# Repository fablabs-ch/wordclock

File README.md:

# WordClock

This is our adaptation of the [Javelin's Word Clock][javelin-word-clock].

## Documentation

You can find all the documentation in the [Wiki][wiki]

* [User manual][user-manual]

## Initial development

The initial development take place on different platforms:

- [Trello][trello-fablabs-ch] for the tasks and progression management.
- [Slack's `#fab-jam_make-athon` channel][slack-fab-jam] for discussions.

## License

This work is licensed under a
[Creative Commons Attribution-NonCommercial-ShareAlike 4.0 International License][by-nc-sa].
Some files may be released under a different license. When this is the case the
license is specified in the file header. This is mainly used for software codes
for which Creative Commons licenses are not well suited.

[][by-nc-sa]

[javelin-word-clock]: http://www.instructables.com/id/Javelins-Word-Clock/
[wiki]: https://github.com/fablabs-ch/wordclock/wiki
[user-manual]: https://github.com/fablabs-ch/wordclock/wiki/User-manual
[trello-fablabs-ch]: https://trello.com/fablabsuisses
[slack-fab-jam]: https://fablabs-ch.slack.com/messages/fab-jam_make-athon/details/
[by-nc-sa]: http://creativecommons.org/licenses/by-nc-sa/4.0/

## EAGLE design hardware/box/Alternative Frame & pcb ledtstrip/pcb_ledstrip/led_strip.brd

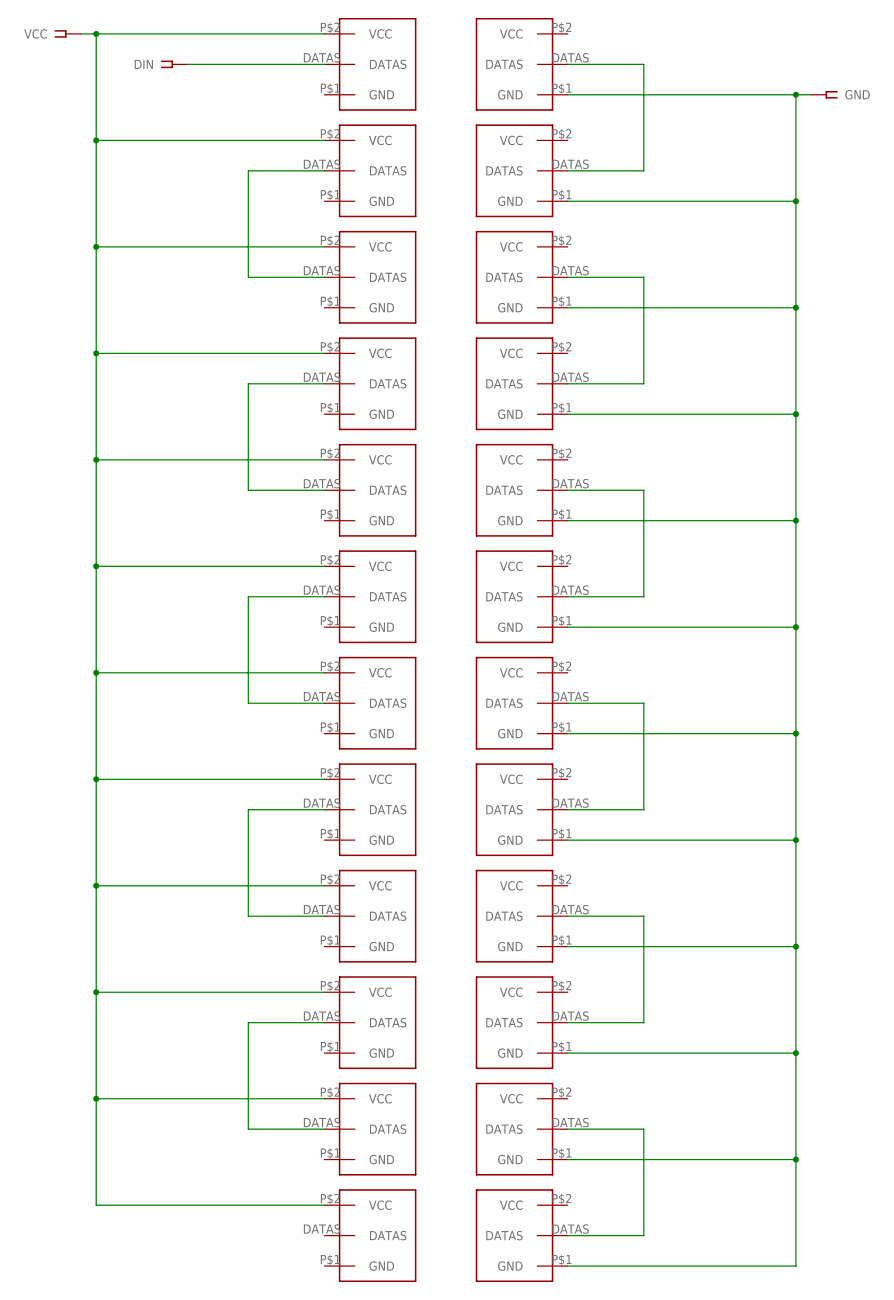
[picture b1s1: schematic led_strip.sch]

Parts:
1: 1; LED_STRIP
2, 3, 4, 5, 6, 7, 8, 9, 10, 11, 12, 13, 14, 15, 16, 17, 18, 19, 20, 21, 22, 23, 24: LED_STRIP
DIN: DATA; SSW-101-02-S-S
GND: GND; SSW-101-02-S-S
VCC: VCC; SSW-101-02-S-S

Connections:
GND: 1.P$1 (GND), 2.P$1 (GND), 3.P$1 (GND), 4.P$1 (GND), 5.P$1 (GND), 6.P$1 (GND), 7.P$1 (GND), 8.P$1 (GND), 9.P$1 (GND), 10.P$1 (GND), 11.P$1 (GND), 12.P$1 (GND), GND.1
unnamed: 13.DATAS, DIN.1
unnamed: 1.DATAS, 2.DATAS
unnamed: 14.DATAS, 15.DATAS
unnamed: 3.DATAS, 4.DATAS
unnamed: 16.DATAS, 17.DATAS
unnamed: 5.DATAS, 6.DATAS
unnamed: 18.DATAS, 19.DATAS
unnamed: 7.DATAS, 8.DATAS
unnamed: 20.DATAS, 21.DATAS
unnamed: 22.DATAS, 23.DATAS
unnamed: 9.DATAS, 10.DATAS
unnamed: 11.DATAS, 12.DATAS
VCC: 13.P$2 (VCC), 14.P$2 (VCC), 15.P$2 (VCC), 16.P$2 (VCC), 17.P$2 (VCC), 18.P$2 (VCC), 19.P$2 (VCC), 20.P$2 (VCC), 21.P$2 (VCC), 22.P$2 (VCC), 23.P$2 (VCC), 24.P$2 (VCC), VCC.1

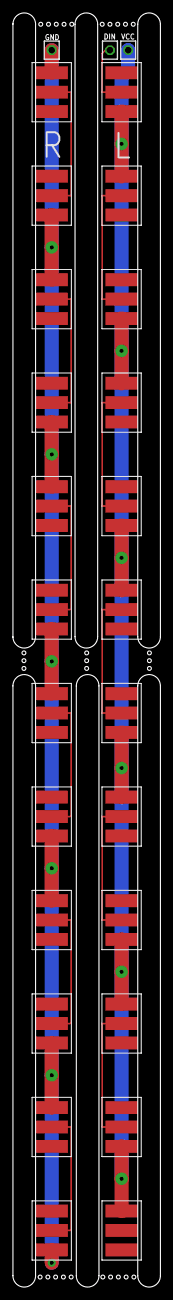
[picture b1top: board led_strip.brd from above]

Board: 2 copper layers, 22.8 x 197.0 mm, 27 parts (0 on the bottom side), 14 nets.

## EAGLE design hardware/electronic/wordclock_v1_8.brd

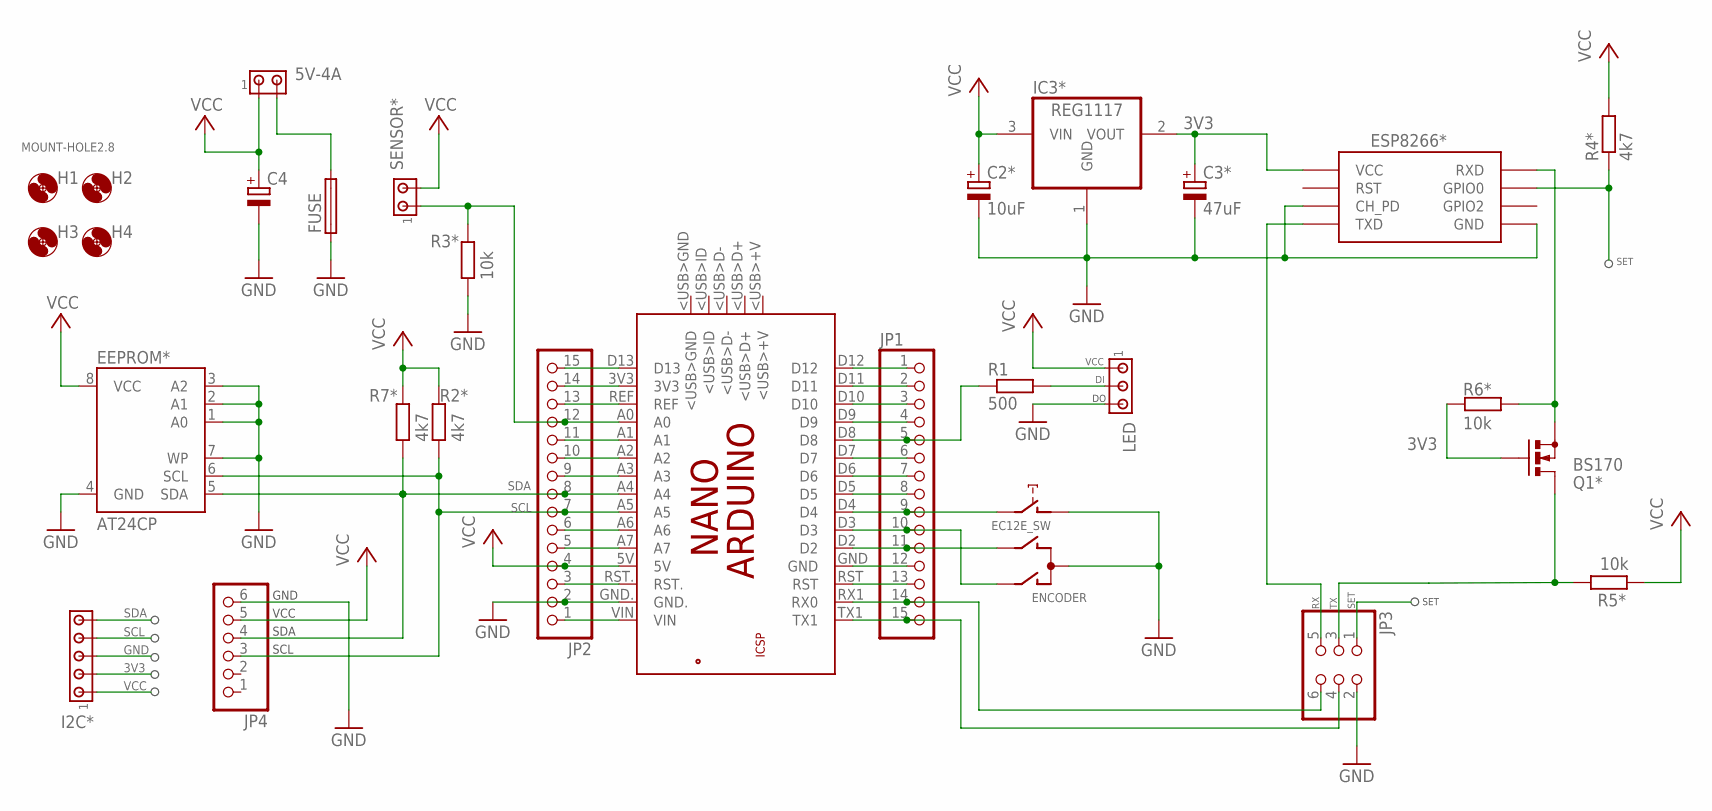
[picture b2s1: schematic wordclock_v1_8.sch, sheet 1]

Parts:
5V-4A: 5V-4A; 1X2MTA
C2*: 10uF; B45181A
C3*: 47uF; B45181A
C4: CPOL-EUE5-10.5; E5-10,5
EEPROM*: AT24CP; DIL08
ENCODER: EC12E_SW; ALPS_EC12E_SW
ESP8266*: ESP01
FUSE: FUSELITTLEFUSE; LITTLEFUSE
H1, H2, H3, H4: MOUNT-HOLE2.8; 2,8
I2C*: MTA05-100; 10X05MTA
IC3*: REG1117; SOT223
JP1, JP2: PINHD-1X15; 1X15
JP3: PINHD-2X3; 2X03
JP4: PINHD-1X6; 1X06
LED: MTA03-156; 1X3MTA
PCB2: ARDUINO_NANO
Q1*: BS170; SOT54E
R1: 500; 0207/7
R2*, R4*, R7*: 4k7; 0207/10
R3*, R5*, R6*: 10k; 0207/10
SENSOR*: MTA02-156; 1X2MTA

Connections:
3V3: C3*.+, ESP8266*.VCC, I2C*.2, IC3*.2 (VOUT), Q1*.G, R6*.1
DI: LED.2, R1.2
GND: C2*.-, C3*.-, C4.-, EEPROM*.1 (A0), EEPROM*.2 (A1), EEPROM*.3 (A2), EEPROM*.4 (GND), EEPROM*.7 (WP), ENCODER.C, ENCODER.D (1), ESP8266*.CH_PD, ESP8266*.GND, FUSE.1, I2C*.3, IC3*.1 (GND), JP2.2, JP3.2, JP4.6, LED.3, PCB2.GND., R3*.1
unnamed: JP1.1, PCB2.D12
unnamed: JP1.2, PCB2.D11
unnamed: JP1.5, PCB2.D8, R1.1
unnamed: 5V-4A.2, FUSE.2
unnamed: ENCODER.B, JP1.11, PCB2.D2
unnamed: ENCODER.A, JP1.10, PCB2.D3
unnamed: ENCODER.E (2), JP1.9, PCB2.D4
unnamed: JP1.3, PCB2.D10
unnamed: JP1.14, JP3.6, PCB2.RX1 (RX0)
unnamed: JP1.15, JP3.4, PCB2.TX1
unnamed: JP2.12, PCB2.A0, R3*.2, SENSOR*.1
unnamed: JP1.4, PCB2.D9
unnamed: JP1.6, PCB2.D7
unnamed: ESP8266*.RX (RXD), Q1*.S, R6*.2
unnamed: JP1.7, PCB2.D6
unnamed: JP1.8, PCB2.D5
unnamed: JP1.12, PCB2.GND
unnamed: JP1.13, PCB2.RST
unnamed: JP2.15, PCB2.D13
unnamed: JP2.14, PCB2.3V3
unnamed: JP2.13, PCB2.REF
unnamed: JP2.11, PCB2.A1
unnamed: JP2.10, PCB2.A2
unnamed: JP2.9, PCB2.A3
unnamed: JP2.6, PCB2.A6
unnamed: JP2.5, PCB2.A7
unnamed: JP2.3, PCB2.RST.
unnamed: JP2.1, PCB2.VIN
RX: ESP8266*.TX (TXD), JP3.5
SCL: EEPROM*.6 (SCL), I2C*.4, JP2.7, JP4.3, PCB2.A5, R2*.1
SDA: EEPROM*.5 (SDA), I2C*.5, JP2.8, JP4.4, PCB2.A4, R7*.1
SET: ESP8266*.GPIO0, JP3.1, R4*.1
TX: JP3.3, Q1*.D, R5*.2
VCC: 5V-4A.1, C2*.+, C4.+, EEPROM*.8 (VCC), I2C*.1, IC3*.3 (VIN), JP2.4, JP4.5, LED.1, PCB2.5V, R2*.2, R4*.2, R5*.1, R7*.2, SENSOR*.2

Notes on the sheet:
SDA
SCL
GND
VCC
SET

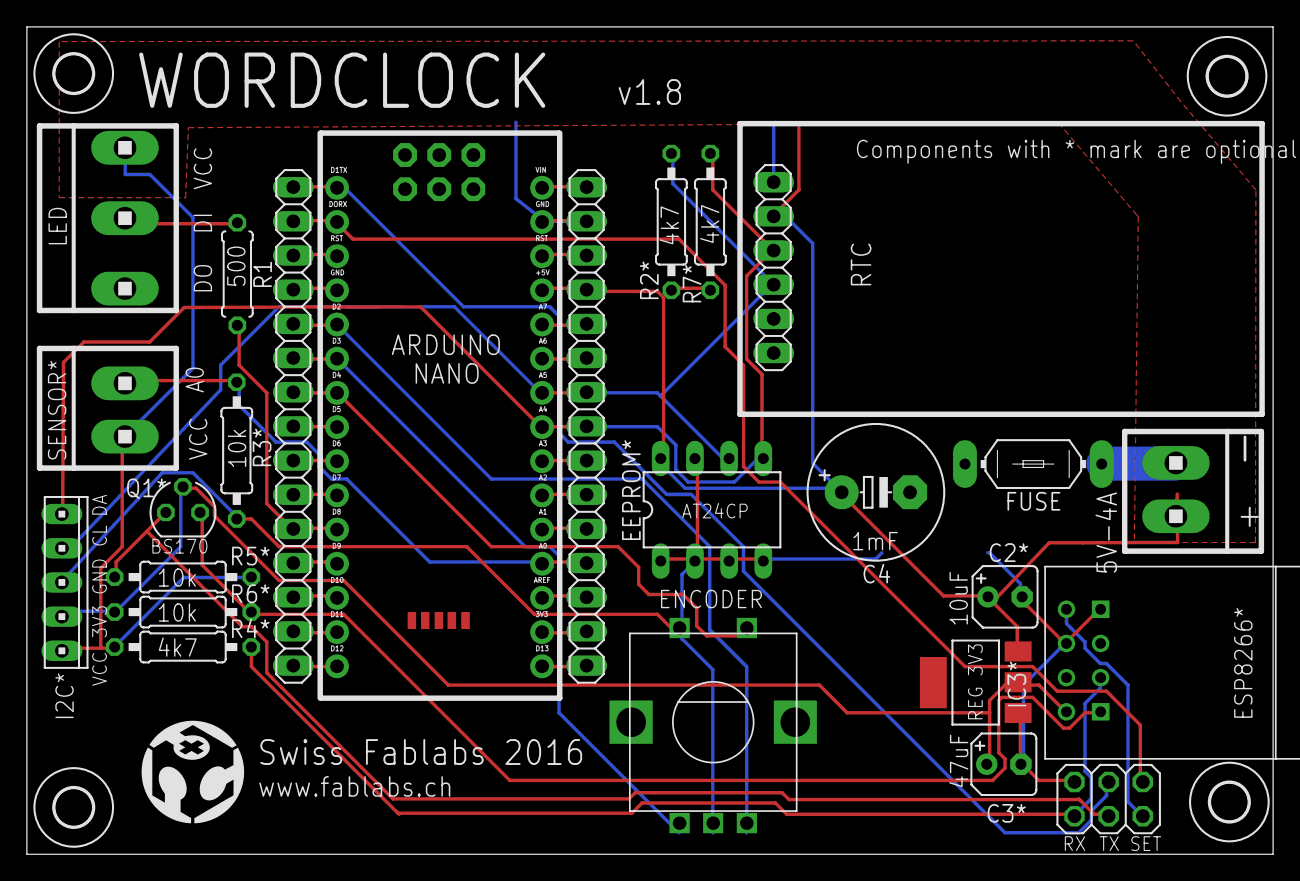
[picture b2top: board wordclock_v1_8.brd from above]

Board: 2 copper layers, 92.6 x 61.5 mm, 29 parts (0 on the bottom side), 37 nets.

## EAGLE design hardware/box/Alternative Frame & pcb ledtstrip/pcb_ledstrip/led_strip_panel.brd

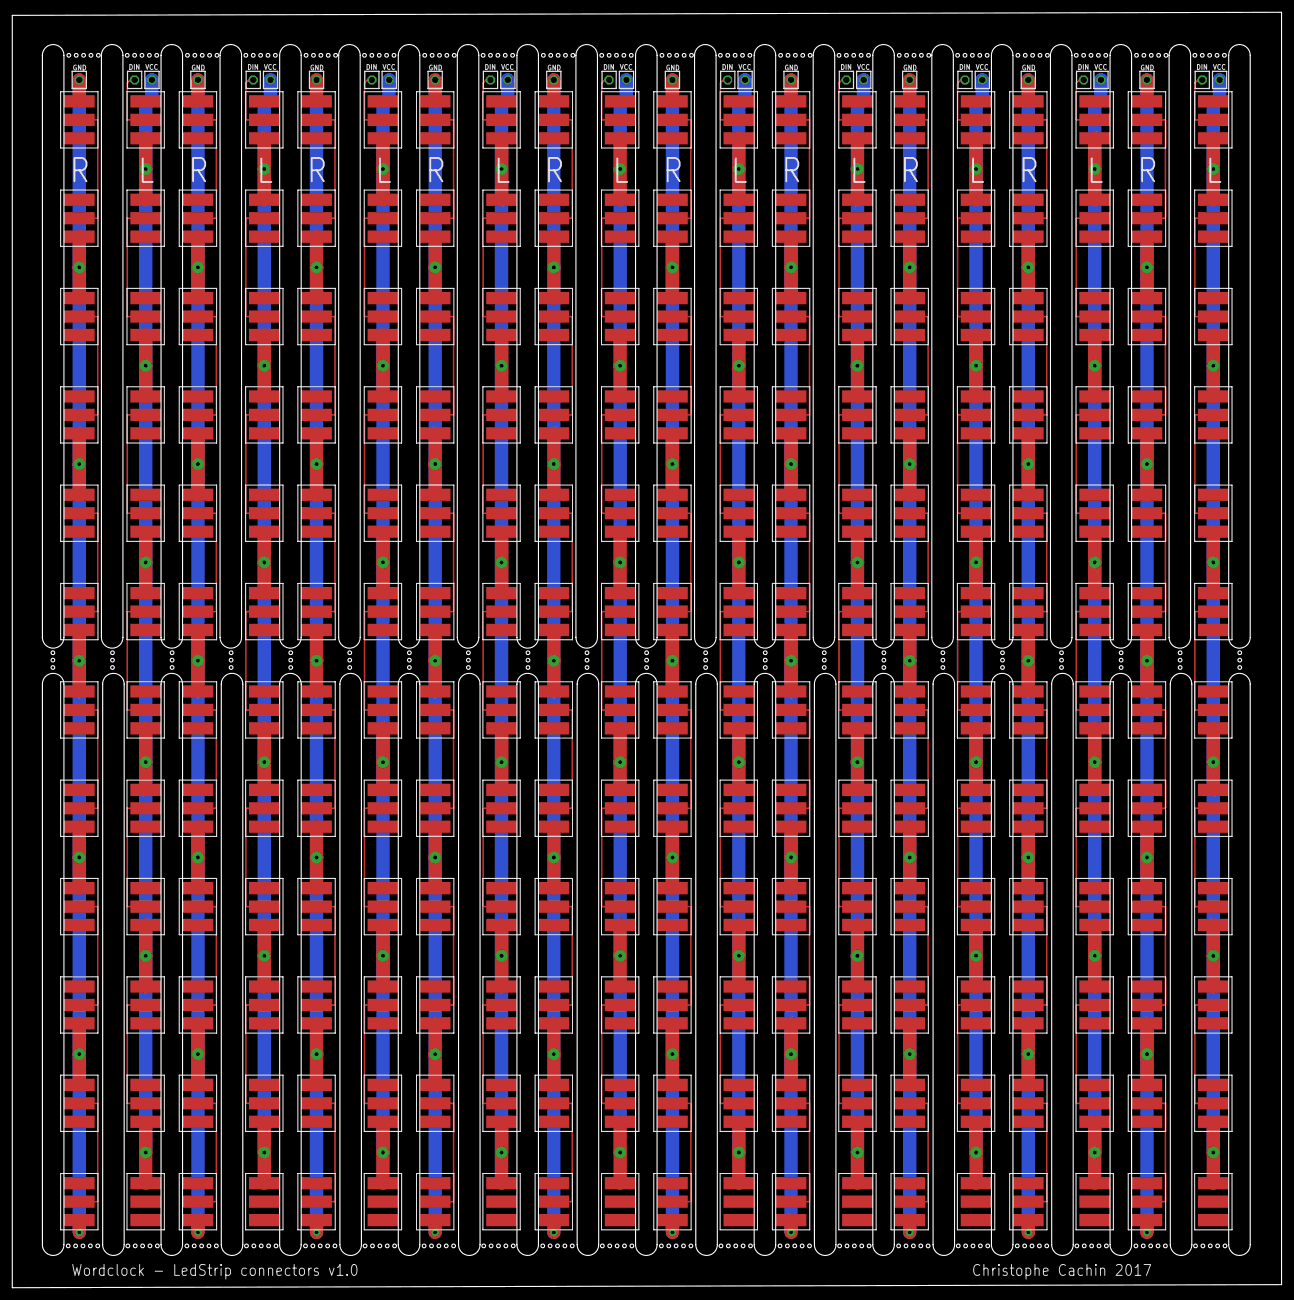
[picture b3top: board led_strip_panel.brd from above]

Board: 2 copper layers, 206.5 x 207.5 mm, 270 parts (0 on the bottom side), 140 nets.

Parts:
1, 25, 49, 73, 97, 121, 145, 169, 193, 217: 1; LED_STRIP
2, 3, 4, 5, 6, 7, 8, 9, 10, 11, 12, 13, 14, 15, 16, 17, 18, 19, 20, 21, 22, 23, 24, 26, 27, 28, 29, 30, 31, 32, 33, 34, 35, 36, 37, 38, 39, 40, 41, 42, 43, 44, 45, 46, 47, 48, 50, 51, 52, 53, 54, 55, 56, 57, 58, 59, 60, 61, 62, 63, 64, 65, 66, 67, 68, 69, 70, 71, 72, 74, 75, 76, 77, 78, 79, 80, 81, 82, 83, 84, 85, 86, 87, 88, 89, 90, 91, 92, 93, 94, 95, 96, 98, 99, 100, 101, 102, 103, 104, 105, 106, 107, 108, 109, 110, 111, 112, 113, 114, 115, 116, 117, 118, 119, 120, 122, 123, 124, 125, 126, 127, 128, 129, 130, 131, 132, 133, 134, 135, 136, 137, 138, 139, 140, 141, 142, 143, 144, 146, 147, 148, 149, 150, 151, 152, 153, 154, 155, 156, 157, 158, 159, 160, 161, 162, 163, 164, 165, 166, 167, 168, 170, 171, 172, 173, 174, 175, 176, 177, 178, 179, 180, 181, 182, 183, 184, 185, 186, 187, 188, 189, 190, 191, 192, 194, 195, 196, 197, 198, 199, 200, 201, 202, 203, 204, 205, 206, 207, 208, 209, 210, 211, 212, 213, 214, 215, 216, 218, 219, 220, 221, 222, 223, 224, 225, 226, 227, 228, 229, 230, 231, 232, 233, 234, 235, 236, 237, 238, 239, 240: LED_STRIP
DIN, DIN1, DIN2, DIN3, DIN4, DIN5, DIN6, DIN7, DIN8, DIN9: DATA; SSW-101-02-S-S
GND, GND1, GND2, GND3, GND4, GND5, GND6, GND7, GND8, GND9: GND; SSW-101-02-S-S
VCC, VCC1, VCC2, VCC3, VCC4, VCC5, VCC6, VCC7, VCC8, VCC9: VCC; SSW-101-02-S-S

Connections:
GND: 1.P$1, 2.P$1, 3.P$1, 4.P$1, 5.P$1, 6.P$1, 7.P$1, 8.P$1, 9.P$1, 10.P$1, 11.P$1, 12.P$1, GND.1
GND1: 25.P$1, 26.P$1, 27.P$1, 28.P$1, 36.P$1, 42.P$1, 43.P$1, 44.P$1, 45.P$1, 46.P$1, 47.P$1, 48.P$1, GND1.1
GND2: 49.P$1, 50.P$1, 51.P$1, 52.P$1, 60.P$1, 66.P$1, 67.P$1, 68.P$1, 69.P$1, 70.P$1, 71.P$1, 72.P$1, GND2.1
GND3: 73.P$1, 74.P$1, 75.P$1, 76.P$1, 84.P$1, 90.P$1, 91.P$1, 92.P$1, 93.P$1, 94.P$1, 95.P$1, 96.P$1, GND3.1
GND4: 97.P$1, 98.P$1, 99.P$1, 100.P$1, 108.P$1, 114.P$1, 115.P$1, 116.P$1, 117.P$1, 118.P$1, 119.P$1, 120.P$1, GND4.1
GND5: 121.P$1, 122.P$1, 123.P$1, 124.P$1, 132.P$1, 138.P$1, 139.P$1, 140.P$1, 141.P$1, 142.P$1, 143.P$1, 144.P$1, GND5.1
GND6: 145.P$1, 146.P$1, 147.P$1, 148.P$1, 156.P$1, 162.P$1, 163.P$1, 164.P$1, 165.P$1, 166.P$1, 167.P$1, 168.P$1, GND6.1
GND7: 169.P$1, 170.P$1, 171.P$1, 172.P$1, 180.P$1, 186.P$1, 187.P$1, 188.P$1, 189.P$1, 190.P$1, 191.P$1, 192.P$1, GND7.1
GND8: 193.P$1, 194.P$1, 195.P$1, 196.P$1, 204.P$1, 210.P$1, 211.P$1, 212.P$1, 213.P$1, 214.P$1, 215.P$1, 216.P$1, GND8.1
GND9: 217.P$1, 218.P$1, 219.P$1, 220.P$1, 228.P$1, 234.P$1, 235.P$1, 236.P$1, 237.P$1, 238.P$1, 239.P$1, 240.P$1, GND9.1
unnamed: 13.DATAS, DIN.1
unnamed: 1.DATAS, 2.DATAS
unnamed: 14.DATAS, 15.DATAS
unnamed: 3.DATAS, 4.DATAS
unnamed: 16.DATAS, 17.DATAS
unnamed: 5.DATAS, 6.DATAS
unnamed: 18.DATAS, 19.DATAS
unnamed: 7.DATAS, 8.DATAS
unnamed: 20.DATAS, 21.DATAS
unnamed: 22.DATAS, 23.DATAS
unnamed: 9.DATAS, 10.DATAS
unnamed: 11.DATAS, 12.DATAS
unnamed: 29.DATAS, DIN1.1
unnamed: 25.DATAS, 36.DATAS
unnamed: 30.DATAS, 31.DATAS
unnamed: 42.DATAS, 43.DATAS
unnamed: 32.DATAS, 33.DATAS
unnamed: 44.DATAS, 45.DATAS
unnamed: 34.DATAS, 35.DATAS
unnamed: 46.DATAS, 47.DATAS
unnamed: 37.DATAS, 38.DATAS
unnamed: 39.DATAS, 40.DATAS
unnamed: 26.DATAS, 48.DATAS
unnamed: 27.DATAS, 28.DATAS
unnamed: 53.DATAS, DIN2.1
unnamed: 49.DATAS, 60.DATAS
unnamed: 54.DATAS, 55.DATAS
unnamed: 66.DATAS, 67.DATAS
unnamed: 56.DATAS, 57.DATAS
unnamed: 68.DATAS, 69.DATAS
unnamed: 58.DATAS, 59.DATAS
unnamed: 70.DATAS, 71.DATAS
unnamed: 61.DATAS, 62.DATAS
unnamed: 63.DATAS, 64.DATAS
unnamed: 50.DATAS, 72.DATAS
unnamed: 51.DATAS, 52.DATAS
unnamed: 77.DATAS, DIN3.1
unnamed: 73.DATAS, 84.DATAS
unnamed: 78.DATAS, 79.DATAS
unnamed: 90.DATAS, 91.DATAS
unnamed: 80.DATAS, 81.DATAS
unnamed: 92.DATAS, 93.DATAS
unnamed: 82.DATAS, 83.DATAS
unnamed: 94.DATAS, 95.DATAS
unnamed: 85.DATAS, 86.DATAS
unnamed: 87.DATAS, 88.DATAS
unnamed: 74.DATAS, 96.DATAS
unnamed: 75.DATAS, 76.DATAS
unnamed: 101.DATAS, DIN4.1
unnamed: 97.DATAS, 108.DATAS
unnamed: 102.DATAS, 103.DATAS
unnamed: 114.DATAS, 115.DATAS
unnamed: 104.DATAS, 105.DATAS
unnamed: 116.DATAS, 117.DATAS
unnamed: 106.DATAS, 107.DATAS
unnamed: 118.DATAS, 119.DATAS
unnamed: 109.DATAS, 110.DATAS
unnamed: 111.DATAS, 112.DATAS
unnamed: 98.DATAS, 120.DATAS
unnamed: 99.DATAS, 100.DATAS
unnamed: 125.DATAS, DIN5.1
unnamed: 121.DATAS, 132.DATAS
unnamed: 126.DATAS, 127.DATAS
unnamed: 138.DATAS, 139.DATAS
unnamed: 128.DATAS, 129.DATAS
unnamed: 140.DATAS, 141.DATAS
unnamed: 130.DATAS, 131.DATAS
unnamed: 142.DATAS, 143.DATAS
unnamed: 133.DATAS, 134.DATAS
unnamed: 135.DATAS, 136.DATAS
unnamed: 122.DATAS, 144.DATAS
unnamed: 123.DATAS, 124.DATAS
unnamed: 149.DATAS, DIN6.1
unnamed: 145.DATAS, 156.DATAS
unnamed: 150.DATAS, 151.DATAS
unnamed: 162.DATAS, 163.DATAS
unnamed: 152.DATAS, 153.DATAS
unnamed: 164.DATAS, 165.DATAS
unnamed: 154.DATAS, 155.DATAS
unnamed: 166.DATAS, 167.DATAS
unnamed: 157.DATAS, 158.DATAS
unnamed: 159.DATAS, 160.DATAS
unnamed: 146.DATAS, 168.DATAS
unnamed: 147.DATAS, 148.DATAS
unnamed: 173.DATAS, DIN7.1
unnamed: 169.DATAS, 180.DATAS
unnamed: 174.DATAS, 175.DATAS
unnamed: 186.DATAS, 187.DATAS
unnamed: 176.DATAS, 177.DATAS
unnamed: 188.DATAS, 189.DATAS
unnamed: 178.DATAS, 179.DATAS
unnamed: 190.DATAS, 191.DATAS
unnamed: 181.DATAS, 182.DATAS
unnamed: 183.DATAS, 184.DATAS
unnamed: 170.DATAS, 192.DATAS
unnamed: 171.DATAS, 172.DATAS
unnamed: 197.DATAS, DIN8.1
unnamed: 193.DATAS, 204.DATAS
unnamed: 198.DATAS, 199.DATAS
unnamed: 210.DATAS, 211.DATAS
unnamed: 200.DATAS, 201.DATAS
unnamed: 212.DATAS, 213.DATAS
unnamed: 202.DATAS, 203.DATAS
unnamed: 214.DATAS, 215.DATAS
unnamed: 205.DATAS, 206.DATAS
unnamed: 207.DATAS, 208.DATAS
unnamed: 194.DATAS, 216.DATAS
unnamed: 195.DATAS, 196.DATAS
unnamed: 221.DATAS, DIN9.1
unnamed: 217.DATAS, 228.DATAS
unnamed: 222.DATAS, 223.DATAS
unnamed: 234.DATAS, 235.DATAS
unnamed: 224.DATAS, 225.DATAS
unnamed: 236.DATAS, 237.DATAS
unnamed: 226.DATAS, 227.DATAS
unnamed: 238.DATAS, 239.DATAS
unnamed: 229.DATAS, 230.DATAS
unnamed: 231.DATAS, 232.DATAS
unnamed: 218.DATAS, 240.DATAS
unnamed: 219.DATAS, 220.DATAS
VCC: 13.P$2, 14.P$2, 15.P$2, 16.P$2, 17.P$2, 18.P$2, 19.P$2, 20.P$2, 21.P$2, 22.P$2, 23.P$2, 24.P$2, VCC.1
VCC1: 29.P$2, 30.P$2, 31.P$2, 32.P$2, 33.P$2, 34.P$2, 35.P$2, 37.P$2, 38.P$2, 39.P$2, 40.P$2, 41.P$2, VCC1.1
VCC2: 53.P$2, 54.P$2, 55.P$2, 56.P$2, 57.P$2, 58.P$2, 59.P$2, 61.P$2, 62.P$2, 63.P$2, 64.P$2, 65.P$2, VCC2.1
VCC3: 77.P$2, 78.P$2, 79.P$2, 80.P$2, 81.P$2, 82.P$2, 83.P$2, 85.P$2, 86.P$2, 87.P$2, 88.P$2, 89.P$2, VCC3.1
VCC4: 101.P$2, 102.P$2, 103.P$2, 104.P$2, 105.P$2, 106.P$2, 107.P$2, 109.P$2, 110.P$2, 111.P$2, 112.P$2, 113.P$2, VCC4.1
VCC5: 125.P$2, 126.P$2, 127.P$2, 128.P$2, 129.P$2, 130.P$2, 131.P$2, 133.P$2, 134.P$2, 135.P$2, 136.P$2, 137.P$2, VCC5.1
VCC6: 149.P$2, 150.P$2, 151.P$2, 152.P$2, 153.P$2, 154.P$2, 155.P$2, 157.P$2, 158.P$2, 159.P$2, 160.P$2, 161.P$2, VCC6.1
VCC7: 173.P$2, 174.P$2, 175.P$2, 176.P$2, 177.P$2, 178.P$2, 179.P$2, 181.P$2, 182.P$2, 183.P$2, 184.P$2, 185.P$2, VCC7.1
VCC8: 197.P$2, 198.P$2, 199.P$2, 200.P$2, 201.P$2, 202.P$2, 203.P$2, 205.P$2, 206.P$2, 207.P$2, 208.P$2, 209.P$2, VCC8.1
VCC9: 221.P$2, 222.P$2, 223.P$2, 224.P$2, 225.P$2, 226.P$2, 227.P$2, 229.P$2, 230.P$2, 231.P$2, 232.P$2, 233.P$2, VCC9.1

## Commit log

2016-01-18 Add an inital README
2016-01-23 Add layout documentation
2016-01-23 Add total number of LEDs in layout
2016-01-23 Set column number in bold font
2016-01-23 Remove "COL" from tables in layout
2016-01-23 Add leading 0 in row numbers
2016-01-23 Add documentation section in the README
2016-01-23 Add informations about holes in the layout
2016-01-23 Distribute holes and add explanation about it
2016-01-23 Moved `doc/layout` to `layouts/`
2016-01-24 Add SVG generation script
2016-01-24 Change wrong extension of en.csv
2016-01-24 Remove double spaces in raw layouts
2016-01-24 Update layout's README
2016-01-24 Update defaults style of the generation scripts
2016-01-24 Update layout's README TOC
2016-01-24 Correct wrong inner-link
2016-01-24 Correct titles
2016-01-24 Change section to subsections
2016-01-24 Change markup for layout's specificities
2016-01-24 Formating of code samples in layouts README
2016-01-25 Add LICENSE
2016-01-25 Update licensing for file custom license
2016-01-25 Add LICENSE information for generate_svg.py
2016-01-29 start of the arduino code
2016-01-30 rotary encoder implementation
2016-01-30 long press
2016-01-30 display debug
2016-02-06 start of layout fr
2016-02-06 abstract layout
2016-02-06 improve layout
2016-02-07 read input from serial
2016-02-07 french layout
2016-02-07 add comment
2016-02-07 class diagram
2016-02-07 arduino readme
2016-02-07 test with WS2812 lights
2016-02-08 Add `-` between "twenty" and "five"
2016-02-08 Add `en` layout
2016-02-10 test with DS3231
2016-02-21 config and anti rebound
2016-02-21 defered input + layout fix
2016-02-21 manage state change
2016-02-21 change color
2016-02-21 state diagram
2016-02-21 read from external clock
2016-02-21 hsl to hsv
2016-02-25 schematic
2016-03-06 small fixes + schema
2016-03-11 edit time
2016-03-12 update class diagram
2016-03-12 comments
2016-03-12 store config in EEPROM
2016-03-12 fix display bug
2016-03-13 know for rotary encoder
2016-03-13 fix knob hole size
2016-03-21 Correct typo in knob.scad
2016-04-02 Update grid in 12x12
2016-04-02 Add a line for the minutes
2016-04-02 Generate random letters in the layout if not specified
2016-04-02 Add output argument for layout generation script
2016-04-02 Add layout's gitignore
2016-04-02 Update layouts README
2016-04-02 Add generated layouts
2016-04-02 New generated layout at 16.5 interval
2016-04-02 Update EN layout in Arduino code
2016-04-02 Update FR layout in Arduino code
2016-04-02 matrix tester
2016-04-02 improve tester
2016-04-02 fix config
2016-04-02 fix log
2016-04-02 fix memory issue
2016-04-02 memory optimisation
2016-04-02 optimize and fix display bug
2016-04-03 heures
2016-04-03 Update the SVG for the FR layout
2016-04-03 Update Arduino code to support "heures" in plural
2016-04-03 Update layout's folder README
2016-04-03 Update Layout.cpp to add minute on the star
2016-04-05 The bluePrints of the different pieces of the box that fit on two boards. The files contain the entire pieces. NOTE that to fit on two boards some pieces have common sides. These sides should be remo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
2016-04-08 Correct "arduino" -> "Arduino" for linux
2016-04-08 indentation
2016-04-09 memory optimisation + matrix tester included
2016-04-10 digital layout
2016-04-10 digital layout state
2016-04-10 reorganize folders
2016-04-10 wordclock image
2016-04-10 image size reduction
2016-04-10 Schematics
    1er commit des schémas.
    Pas définitif, manque des pull-up sur l’ESP8266 et le mode
    « programmation ».
2016-04-13 Update schematics
2016-04-13 PCB + Latest schematic
2016-04-14 Add jumper to programm ESP
    RX/TX/SET easier to put one pin header instead of three.
2016-04-15 Latest changes
    Placement and size changes:
    - RTC
    - Capacitor
    ———
    - Extend Arduino pins
    - Add and review labels
2016-04-16 Update
    Labels layer positions
2016-05-02 alternative case and led splitter are designed to reduce the fabrication time
2016-05-14 light sensor
2016-06-27 Plans de masse
    - Correction des plans de masse
2016-06-27 V1.8
    - Redis connecteur 3poles
    - Correction overlap Sensor
    - Redimensionnement Sérigraphie
    - Mise en évidence des composants optionnel
    - Ajout d’un plan de masse
2016-06-27 pics
2016-07-04 lien github
    Ajout du lien github sur le pcb
2016-08-11 Photos
    PC avec les composants et les différentes parties du pub
2016-10-01 light sensor event
2016-10-01 photo low res
2016-10-01 fix hours in french
2016-10-01 design updated
2016-10-01 Updated front project image
2016-10-01 Fix file path front image
2016-10-01 FIxed Case sensitive file path
2016-10-01 Rotate image file from README
2016-10-03 wiki image
2016-10-03 default pcb
2016-10-03 default pcbs without photo res
2016-10-03 photo res
2016-10-03 ext mem pic
2016-10-05 optional reversed minutes
2016-10-05 Add ws2812 module
2016-10-05 Implement basic Grid controller
2016-10-06 ready to cut files
2016-10-07 De and dezh layouts
    German and Züritütsch layouts
2016-10-07 Add a space between ist and halb
2016-10-07 Change README image and set ratio to 80% by width
2016-10-08 schema
2016-10-08 LEDs simulator with ANSI color codes
    I wasn't having the LEDs with me, so let's do a linux terminal emulator
    with ANSI color codes
2016-10-08 Add a gitignore
2016-10-08 Improve grid module
2016-10-08 Add a requirements.txt file for the virtual env
2016-10-08 Add support for drawing rectangle border
2016-10-08 Update ws2812
2016-10-08 Make ws2812 pylint OK
2016-10-08 Fix draw_rectangle method
2016-10-08 Implement draw_circle border
2016-10-09 separate libs
2016-10-09 Grid improved
2016-10-09 Draw letters
2016-10-09 Separate chars into its own module
2016-10-09 Handle None in subgrids
2016-10-09 Fix bug with mask
2016-10-09 Remove unneeded space
2016-10-09 Fix bug with letter Z
2016-10-09 Use integer division becaus wipy doesn't support floating one
2016-10-09 Remove letters from demo (too spacy)
2016-10-09 Allow to specify grid reset color
2016-10-09 Create a BaseApplication class
2016-10-09 New meteo module
2016-10-13 led wiring
2016-10-14 Add '-' char symbol
2016-10-14 Better temperature display (centered)
2016-10-14 Fix number '4' representation
2016-10-14 Improve show_icon in meteo
2016-10-14 Align weather icons on the same row
2016-10-14 Update demo of 'meteo' module
2016-10-14 Change meteo icons name
2016-10-14 Reset grids before showing meteo
2016-10-14 Add a run coroutine in BaseApplication
2016-10-14 Add prototype of wordclock application
2016-10-15 Fix coroutine
2016-10-15 Extract controllor to its own module
    Allow to share the same controller between grids.
2016-10-15 Rename wordclock -> main
2016-10-15 Set the overlay as a public member of grid
2016-10-15 Initial attempt of wordclock
2016-10-15 Add untplib module
2016-10-15 Port the code to work on WiPy
2016-10-15 Rename main -> launcher
2016-10-15 run as coroutine in wordclock
2016-10-15 Update launcher with a server for remote control
2016-10-16 Lots of improvements (conf, server, coroutine, …)
2016-10-16 ready to cut for 594x420mm plate
2016-10-16 debug display
2016-10-17 Add time shift to configuration
2016-10-17 Simplify launcher
2016-10-17 Improvement ( too much stuff in it, sorry /o\ )
2016-10-18 remove tests
2016-10-18 take compile time
2016-10-19 assembly
2016-10-19 fix virtual clock for debug
2016-10-21 Fix typo in generate_svg doctstring
2016-10-21 Update .gitignore for python (and virtual environment)
2016-10-21 Adapt generate_svg.py to be used from another module
2016-10-21 Write a service to serve the generator
2016-10-21 First attempt of Dockerization, not working on my computer
    I dont know if it is my computer which has a problem or a docker
    problem.
2016-10-21 Remove additional new line from grid input
2016-10-21 Set a default text for grid textarea
2016-10-22 Remove '|' separators in raw grids
2016-10-22 Adapt the code to deal with raw grid without separators
2016-10-22 Improve and comments the generate_svg
2016-10-22 Fix issue with online service grid parsing
2016-10-23 Reorder and remove unused imports
2016-10-23 Add buttons to load pre-existing languages
2016-10-24 Install inkscape in the container
2016-10-24 Make Flask listen on all interfaces
2016-10-30 Use normal python container instead of alpine
    Probably the source of the bug with inkscape
2016-10-30 Clean service.py
2016-10-30 Add fonttools dependency
2016-10-30 Use correct form encoding for sending files
2016-10-30 Add support for different fonts
2016-10-30 Better explanation about font file
2016-10-30 Fix code comment and formatting
2016-10-30 Update the README with information for using the web interface.
2016-11-03 Handle the case where font file are not UTF-8 encoded on windows
2016-11-09 template for layout
2016-11-12 small warning comment
2016-11-12 Photo sensor tester
2016-11-12 default font for generator
2016-11-13 fix bug
2016-11-13 update knob size
2016-11-13 change form
2016-11-13 progress on preview
2016-11-13 preview display
2016-11-14 adjust knob
2016-11-14 fix design
2016-11-14 fix new line
2016-11-14 rename button
2016-11-21 remove mistake
2016-11-21 fr layout + remove logo
2016-11-23 ready to cut
2016-11-25 auto light limit
2016-12-16 [TASK] Load layout for both languages FR and EN
2016-12-16 [TASK] Correct the English layout
2016-12-17 [BUGFIX] Add one hour after 34 minutes
    Only add one hour after 34 Minutes not 30
2016-12-18 Remove ifdef in layout
2017-03-16 german layout
2017-03-18 update de layout comment
2017-05-05 Fix
    Fix:
    - ESP CH_PD pin pull up #21
    - Wire RX/TX #20
    - Fix main PCB label #10
2017-05-05 Basic PCB
    Created basic pcbs without ESP, I2C, EEPROM, SENSOR just essential
    things to make it work basically.
    -> Create a basic PCB #16
2017-07-15 motion detection
2017-07-15 disable motion sensor by default
2017-08-27 overflow issue
2017-10-04 Add gerber file
    Add gerber files for production
2018-03-15 New frame and pcb for ledstrip
    Save 2 hours with ledstrip soldering
